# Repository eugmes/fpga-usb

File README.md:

# USB Interface Extension
This is a small board that uses MAX3453E chip to add a USB interface for an FPGA board.
This extension is designed to fit into an extension connector on Numato Mimas V2 FPGA board, but it
probably could be used with other boards that use 6x2 connectors (PMOD) or as a MAX3453E breakout board.

# Connector Pinout

| Pin    | Function | Description                           |
|--------|----------|---------------------------------------|
| 1      | ENUM     | Enumerate function select input       |
| 2      | BD       | Bus detection output                  |
| 3      | RCV      | Differential receiver output          |
| 4      | NC       | No connection                         |
| 5      | V-       | Negative receiver output/driver input |
| 6      | V+       | Positive receiver output/driver input |
| 7      | SUS      | Suspend input                         |
| 8      | #OE      | Output enable                         |
| 9, 10  | GND      | Ground                                |
| 11, 12 | VCC      | Logic supply (1.65V to 3.6V)          |

See also MAX3453E datasheet.

# PCB Layout
The PCB layout project is also shared on [OSH Park](https://oshpark.com/projects/5NEpfuXA).

# License
<br />
<span xmlns:dct="http://purl.org/dc/terms/" property="dct:title">USB Interface Extension</span>
by <span xmlns:cc="http://creativecommons.org/ns#" property="cc:attributionName">Ievgenii Meshcheriakov</span>
is licensed under a <a rel="license" href="http://creativecommons.org/licenses/by-sa/4.0/">Creative Commons Attribution-ShareAlike 4.0 International License</a>.

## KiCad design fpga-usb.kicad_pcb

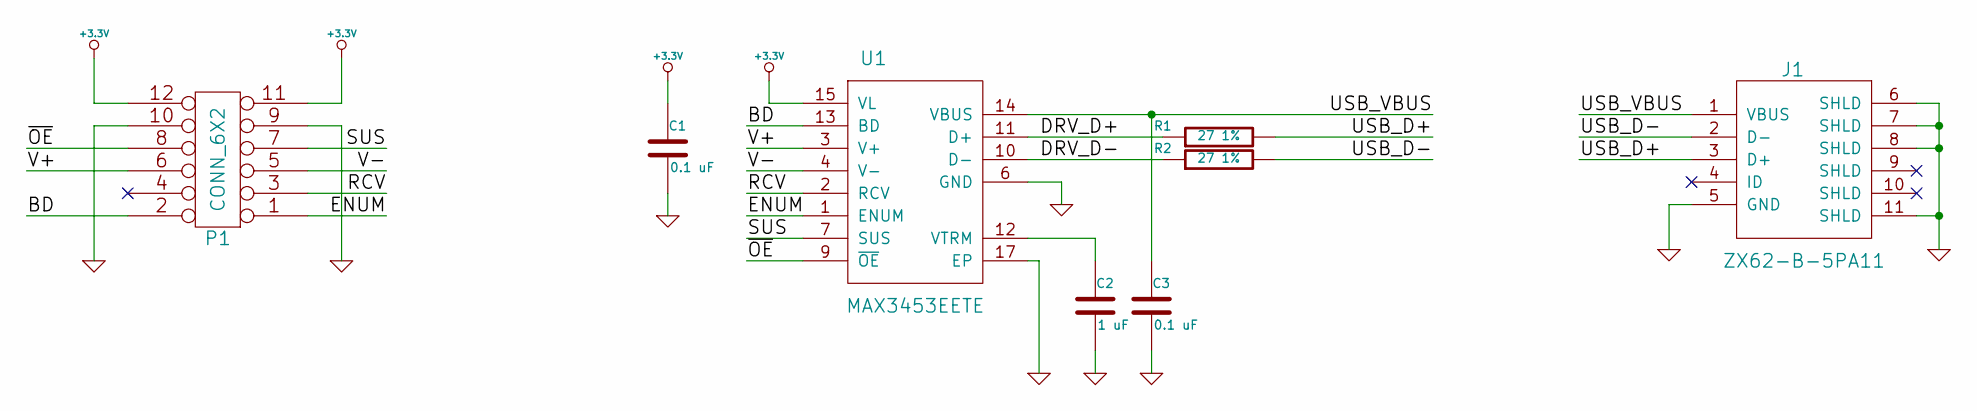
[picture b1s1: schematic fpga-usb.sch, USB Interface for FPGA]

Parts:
C1, C3: 0.1 uF; C0402
C2: 1 uF; C0402
J1: ZX62-B-5PA11
P1: CONN_6X2; pin_array_6x2
R1, R2: 27 1%; R0402
U1: MAX3453EETE; QFN-16-1EP_3x3mm_Pitch0.5mm

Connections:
+3.3V: C1.1, P1.11, P1.12, U1.15 (VL)
/BD: P1.2, U1.13 (BD)
/DRV_D+: R1.1, U1.11 (D+)
/DRV_D-: R2.1, U1.10 (D-)
/ENUM: P1.1, U1.1 (ENUM)
/RCV: P1.3, U1.2 (RCV)
/SUS: P1.7, U1.7 (SUS)
/USB_D+: J1.3 (D+), R1.2
/USB_D-: J1.2 (D-), R2.2
/USB_VBUS: C3.1, J1.1 (VBUS), U1.14 (VBUS)
/V+: P1.6, U1.3 (V+)
/V-: P1.5, U1.4 (V-)
/~OE: P1.8, U1.9 (~OE)
GND: C1.2, C2.2, C3.2, J1.5 (GND), J1.6 (SHLD), J1.7 (SHLD), J1.8 (SHLD), J1.11 (SHLD), P1.9, P1.10, U1.6 (GND), U1.17 (EP)
unnamed: C2.1, U1.12 (VTRM)

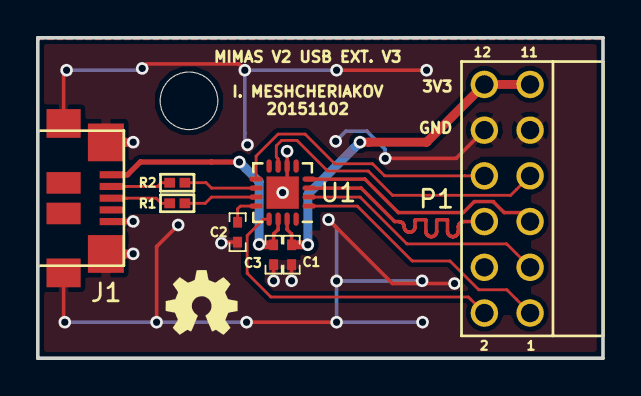
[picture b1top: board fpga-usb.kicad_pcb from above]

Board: 2 copper layers, 31.4 x 17.8 mm, 8 parts (0 on the bottom side), 15 nets.

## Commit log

2015-09-28 Initial version
2015-09-28 Add bottom mask layer
2015-09-28 Update text to indicate V2
2015-10-12 Add PDF of the schematic
2015-11-01 Use MAX3453EETE instead of a discontinued part
    This commit updates schematic only.
2015-11-01 Annotate the schematic and assign footprint to the IC
2015-11-01 Fill-in page info
2015-11-01 Modify layout to use new part
2015-11-01 Select bottom solder mask for plotting
2015-11-03 Add licensing info to the schematic
2015-11-03 Add correct date
2015-11-03 Add title block to the layout
2015-11-03 Update the schematic PDF
2015-11-08 Update README.md
    Fix a typo and and a note that this board can be used as PMOD extension or a breakout board.

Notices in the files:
fpga-usb.kicad_pcb:
This work is licensed under a Attribution-ShareAlike 4.0 International License.
